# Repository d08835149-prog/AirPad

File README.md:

# AirPad

AirPad is a 16-key macropad with an OLED display, powered by a XIAO RP2040.

I made it mainly for shortcuts and programs I use often on my computer.
It uses QMK firmware.

## Features

- 16 mechanical keys
- 0.91" OLED display
- XIAO RP2040
- 4x4 key matrix
- Custom PCB
- Custom case
- QMK firmware
- Shortcuts for Windows, programs, and YouTube

## CAD Model

I designed the case in Onshape.

The case has a bottom part and a top plate, with space for the PCB, switches, OLED, and the USB-C port.

.png)

## PCB

I made the PCB in KiCad.

It uses a 4x4 matrix with 16 switches and 16 1N4148 diodes.

### Schematic

### PCB

## Firmware

AirPad uses QMK firmware.

The keys are:

| | | | |
|---|---|---|---|
| Calculator | Volume + | Volume - | Screenshot |
| Copy | Paste | VS Code | Notepad |
| Discord | File Explorer | Undo | Redo |
| YouTube Mute | Play/Pause | Previous Video | Next Video |

Some keys use normal keyboard shortcuts, while the program keys can open VS Code, Notepad, Discord, and File Explorer.

### OLED

The OLED normally shows:

`AIRPAD`

`READY`

When I press a key, it shows what that key does. For example, pressing the copy key changes the display to `COPY`.

## BOM

- 16x Mechanical switches
- 16x Keycaps
- 16x 1N4148 diodes
- 1x XIAO RP2040
- 1x 0.91" OLED display
- 1x Custom PCB
- 1x 3D printed case

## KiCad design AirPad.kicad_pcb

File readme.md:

# airpad

*A short description of the keyboard/project*

* Keyboard Maintainer: [MinJae](https://github.com/MinJae)
* Hardware Supported: *The PCBs, controllers supported*
* Hardware Availability: *Links to where you can find this hardware*

Make example for this keyboard (after setting up your build environment):

    make airpad:default

Flashing example for this keyboard:

    make airpad:default:flash

See the [build environment setup](https://docs.qmk.fm/#/getting_started_build_tools) and the [make instructions](https://docs.qmk.fm/#/getting_started_make_guide) for more information. Brand new to QMK? Start with our [Complete Newbs Guide](https://docs.qmk.fm/#/newbs).

## Bootloader

Enter the bootloader in 3 ways:

* **Bootmagic reset**: Hold down the key at (0,0) in the matrix (usually the top left key or Escape) and plug in the keyboard
* **Physical reset button**: Briefly press the button on the back of the PCB - some may have pads you must short instead
* **Keycode in layout**: Press the key mapped to `QK_BOOT` if it is available

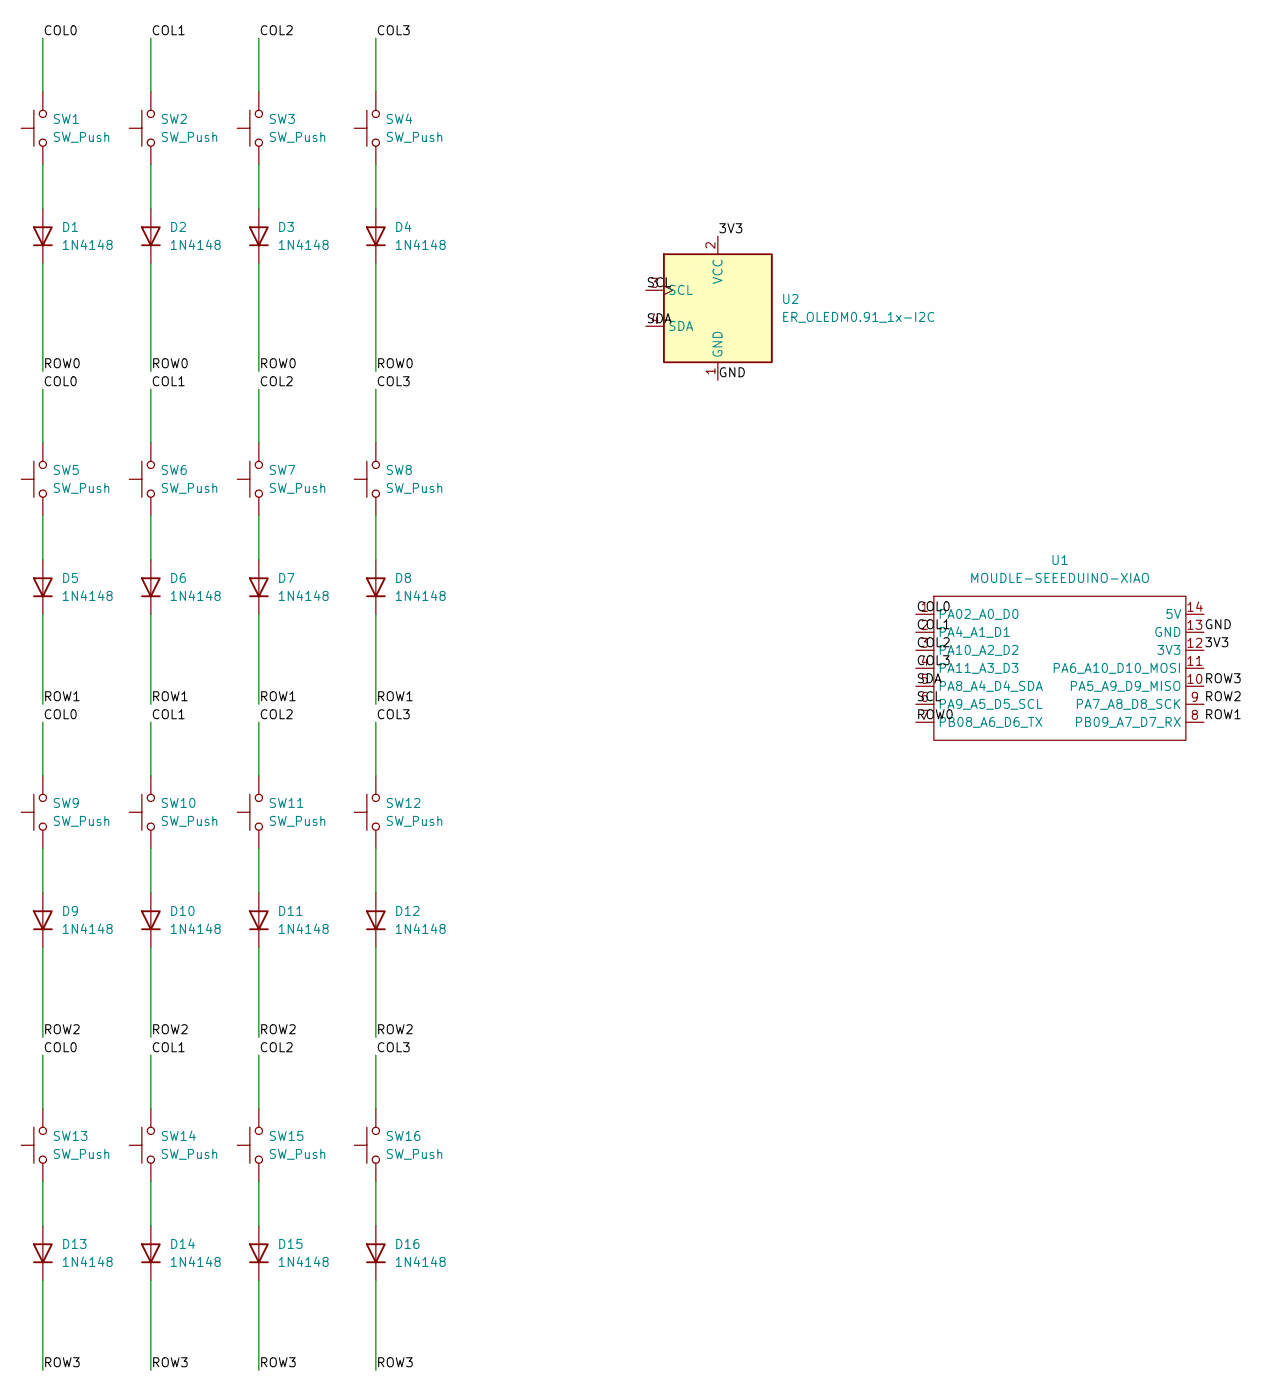
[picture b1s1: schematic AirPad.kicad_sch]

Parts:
D1, D2, D3, D4, D5, D6, D7, D8, D9, D10, D11, D12, D13, D14, D15, D16: 1N4148; D_DO-35_SOD27_P7.62mm_Horizontal
SW1, SW2, SW3, SW4, SW5, SW6, SW7, SW8, SW9, SW10, SW11, SW12, SW13, SW14, SW15, SW16: SW_Push; SW_Cherry_MX_1.00u_PCB
U1: MOUDLE-SEEEDUINO-XIAO; XIAO-Generic-Hybrid-14P-2.54-21X17.8MM
U2: ER_OLEDM0.91_1x-I2C

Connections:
/3V3: U1.12 (3V3), U2.2 (VCC)
/COL0: SW1.2, SW5.2, SW9.2, SW13.2, U1.1 (PA02_A0_D0)
/COL1: SW2.2, SW6.2, SW10.2, SW14.2, U1.2 (PA4_A1_D1)
/COL2: SW3.2, SW7.2, SW11.2, SW15.2, U1.3 (PA10_A2_D2)
/COL3: SW4.2, SW8.2, SW12.2, SW16.2, U1.4 (PA11_A3_D3)
/GND: U1.13 (GND), U2.1 (GND)
/ROW0: D1.1 (K), D2.1 (K), D3.1 (K), D4.1 (K), U1.7 (PB08_A6_D6_TX)
/ROW1: D5.1 (K), D6.1 (K), D7.1 (K), D8.1 (K), U1.8 (PB09_A7_D7_RX)
/ROW2: D9.1 (K), D10.1 (K), D11.1 (K), D12.1 (K), U1.9 (PA7_A8_D8_SCK)
/ROW3: D13.1 (K), D14.1 (K), D15.1 (K), D16.1 (K), U1.10 (PA5_A9_D9_MISO)
/SCL: U1.6 (PA9_A5_D5_SCL), U2.3 (SCL)
/SDA: U1.5 (PA8_A4_D4_SDA), U2.4 (SDA)
unnamed: D1.2 (A), SW1.1
unnamed: D2.2 (A), SW2.1
unnamed: D3.2 (A), SW3.1
unnamed: D4.2 (A), SW4.1
unnamed: D5.2 (A), SW5.1
unnamed: D6.2 (A), SW6.1
unnamed: D7.2 (A), SW7.1
unnamed: D8.2 (A), SW8.1
unnamed: D9.2 (A), SW9.1
unnamed: D10.2 (A), SW10.1
unnamed: D11.2 (A), SW11.1
unnamed: D12.2 (A), SW12.1
unnamed: D13.2 (A), SW13.1
unnamed: D14.2 (A), SW14.1
unnamed: D15.2 (A), SW15.1
unnamed: D16.2 (A), SW16.1

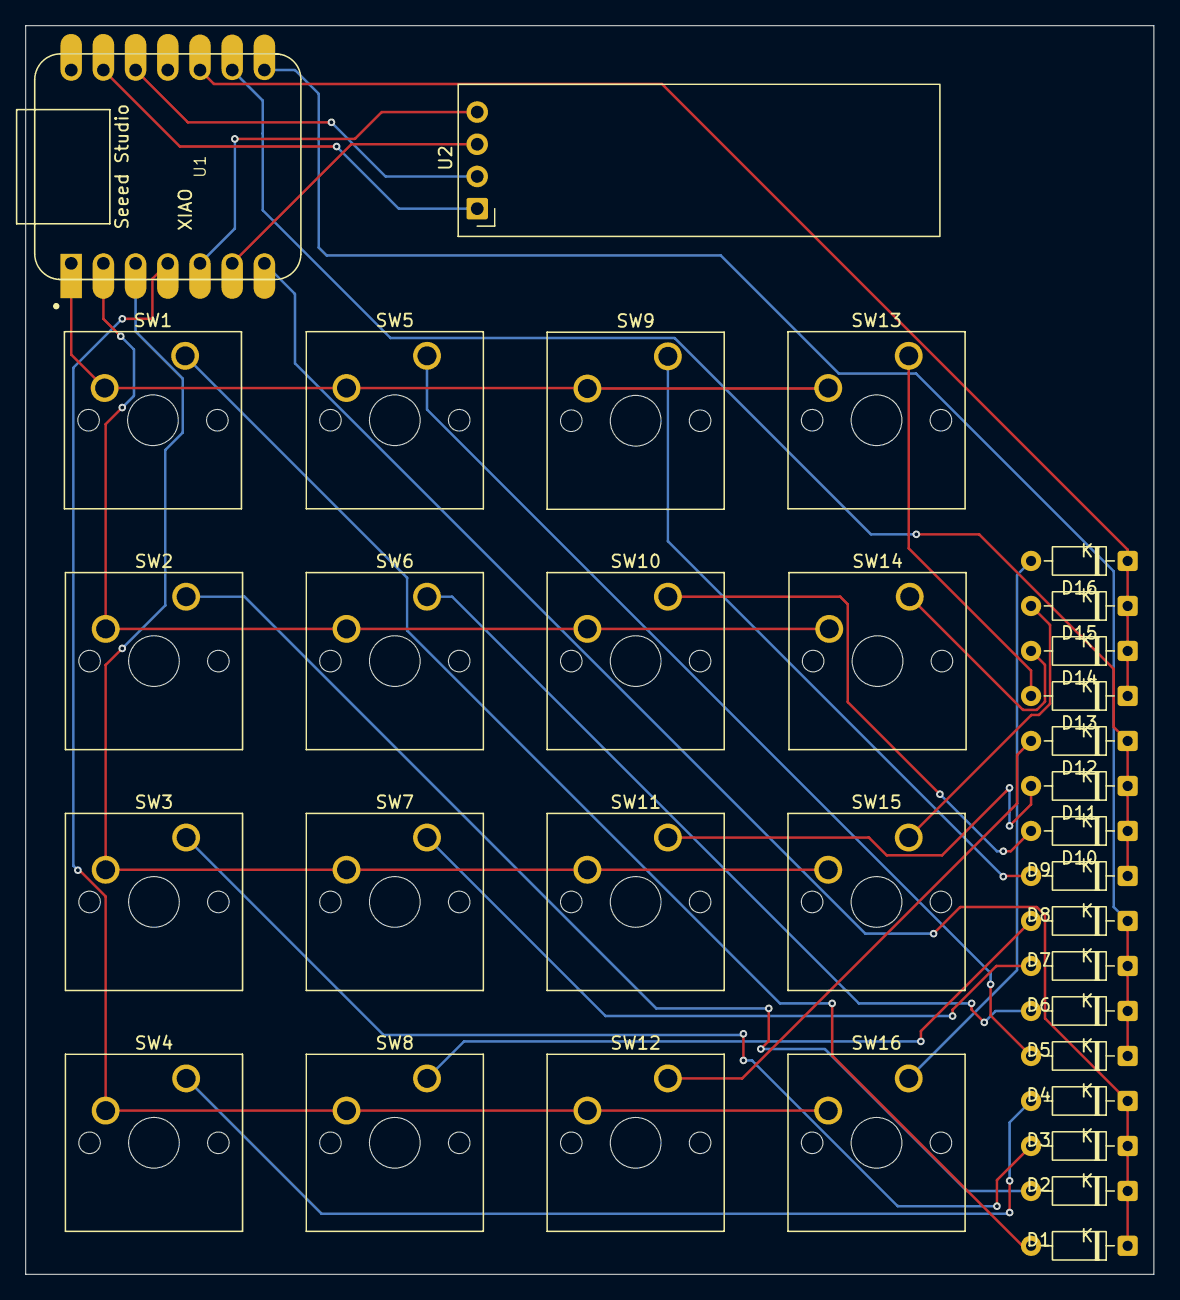
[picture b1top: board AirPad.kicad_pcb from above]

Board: 2 copper layers, 89.0 x 98.5 mm, 34 parts (0 on the bottom side), 28 nets.

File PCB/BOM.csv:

"Reference","Qty","Value","DNP","Exclude from BOM","Exclude from Board","Exclude from Simulation","Exclude from Position Files","Footprint","Datasheet"
"D1,D2,D3,D4,D5,D6,D7,D8,D9,D10,D11,D12,D13,D14,D15,D16","16","1N4148","","","","","${EXCLUDE_FROM_POS_FILES}","Diode_THT:D_DO-35_SOD27_P7.62mm_Horizontal","https://assets.nexperia.com/documents/data-sheet/1N4148_1N4448.pdf"
"SW1,SW2,SW3,SW4,SW5,SW6,SW7,SW8,SW9,SW10,SW11,SW12,SW13,SW14,SW15,SW16","16","SW_Push","","","","","${EXCLUDE_FROM_POS_FILES}","Button_Switch_Keyboard:SW_Cherry_MX_1.00u_PCB",""
"U1","1","MOUDLE-SEEEDUINO-XIAO","","","","","${EXCLUDE_FROM_POS_FILES}","footprints:XIAO-Generic-Hybrid-14P-2.54-21X17.8MM",""
"U2","1","ER_OLEDM0.91_1x-I2C","","","","","${EXCLUDE_FROM_POS_FILES}","Display:ER_OLEDM0.91_1x-I2C","https://www.buydisplay.com/download/manual/ER-OLEDM0.91-1_Da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"
